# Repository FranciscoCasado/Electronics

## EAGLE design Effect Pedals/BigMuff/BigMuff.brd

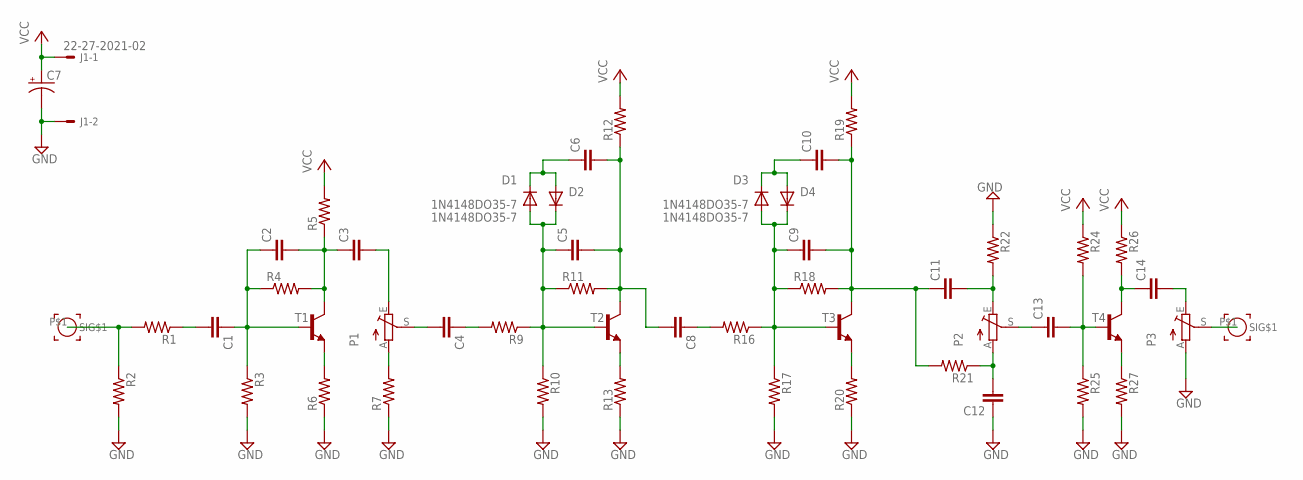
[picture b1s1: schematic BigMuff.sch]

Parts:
C1, C2, C3, C4, C5, C6, C8, C9, C10, C11, C12, C13, C14: C-EU050-024X044-BP; C050-024X044-BP
C7: CPOL-USE2.5-7; E2,5-7
D1, D2, D3, D4: 1N4148DO35-7; DO35-7
J1: 22-27-2021-02; 6410-02
P1, P2, P3: TRIM_EU-S64W; S64W
R1, R2, R3, R4, R5, R6, R7, R9, R10, R11, R12, R13, R16, R17, R18, R19, R20, R21, R22, R24, R25, R26, R27: R-US_0204/5-BP; 0204/5-BP
T1, T2, T3, T4: -NPN-TO92-EBC; TO92-EBC
U$1, U$2: SIGNAL_PAD

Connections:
GND: C7.-, C12.1, J1.2, P3.A, R2.2, R3.2, R6.1, R7.1, R10.2, R13.1, R17.2, R20.1, R22.1, R25.2, R27.2
unnamed: R1.2, R2.1, U$1.P$1
unnamed: C1.2, R1.1
unnamed: C1.1, C2.1, R3.1, R4.1, T1.B
unnamed: C2.2, C3.1, R4.2, R5.1, T1.C
unnamed: R6.2, T1.E
unnamed: P1.A, R7.2
unnamed: C3.2, P1.E
unnamed: C4.2, P1.S
unnamed: C4.1, R9.2
unnamed: C5.1, D1.A, D2.C, R9.1, R10.1, R11.1, T2.B
unnamed: C5.2, C6.2, C8.2, R11.2, R12.1, T2.C
unnamed: R13.2, T2.E
unnamed: C12.2, P2.A, R21.1
unnamed: C11.2, P2.E, R22.2
unnamed: C6.1, D1.C, D2.A
unnamed: C8.1, R16.2
unnamed: C9.1, D3.A, D4.C, R16.1, R17.1, R18.1, T3.B
unnamed: C9.2, C10.2, C11.1, R18.2, R19.1, R21.2, T3.C
unnamed: R20.2, T3.E
unnamed: C10.1, D3.C, D4.A
unnamed: C13.1, P2.S
unnamed: C13.2, R24.2, R25.1, T4.B
unnamed: C14.1, R26.2, T4.C
unnamed: R27.1, T4.E
unnamed: C14.2, P3.E
unnamed: P3.S, U$2.P$1
VCC: C7.+, J1.1, R5.2, R12.2, R19.2, R24.1, R26.1

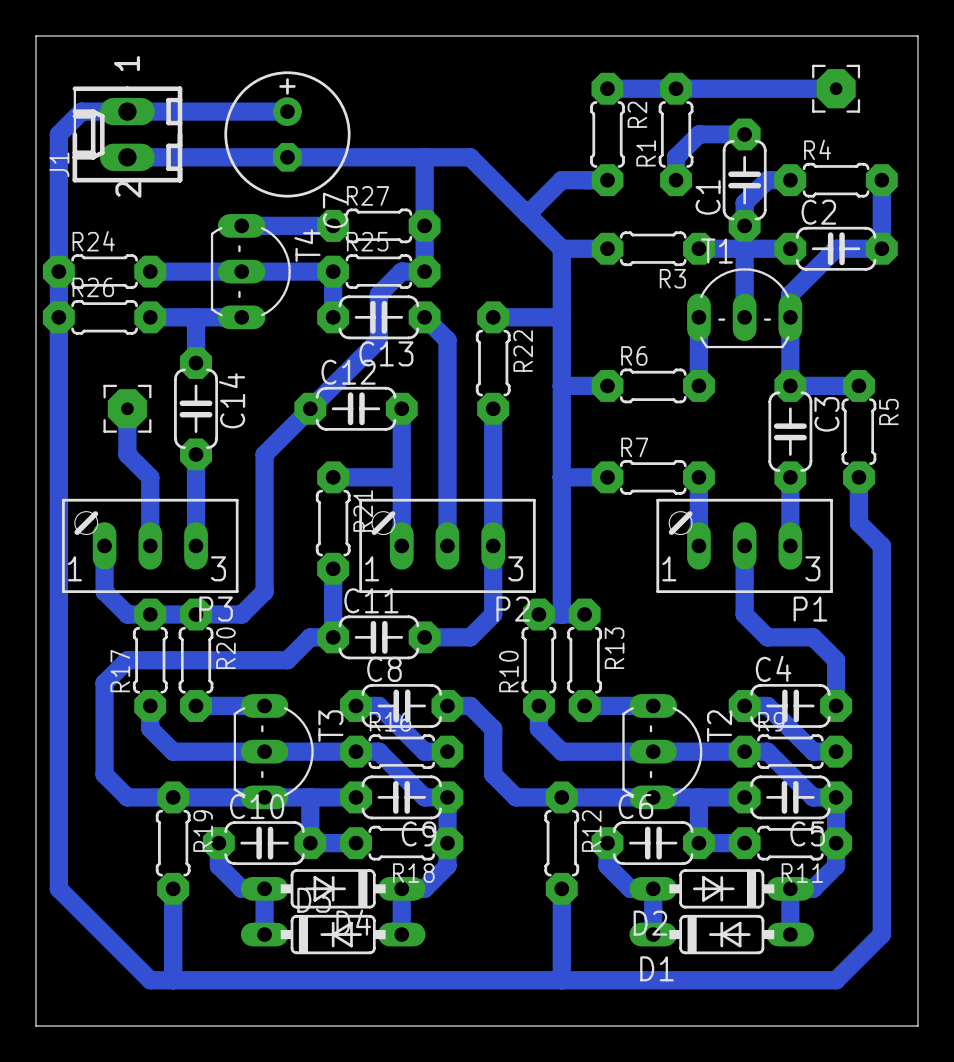
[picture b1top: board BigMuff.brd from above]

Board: 2 copper layers, 49.0 x 55.0 mm, 51 parts (0 on the bottom side), 28 nets.

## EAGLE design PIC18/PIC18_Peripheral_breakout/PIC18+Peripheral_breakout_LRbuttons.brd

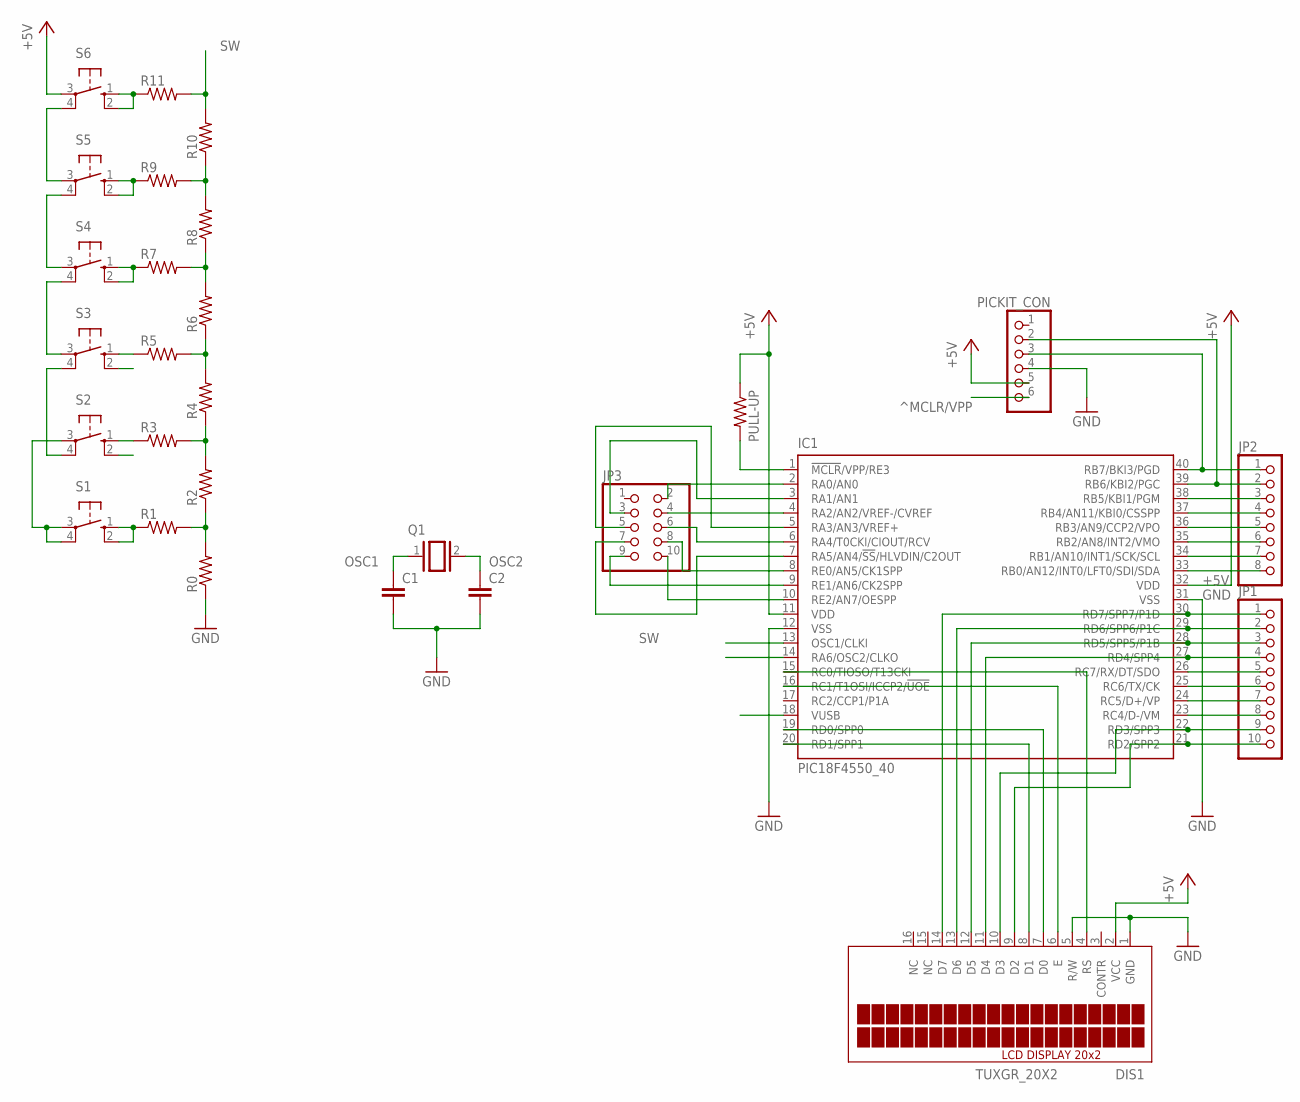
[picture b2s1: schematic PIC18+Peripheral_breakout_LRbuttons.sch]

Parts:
C1, C2: C-EUC1206; C1206
DIS1: TUXGR_20X2
IC1: PIC18F4550_40; DIL40
JP1: PINHD-1X10; 1X10
JP2: PINHD-1X8; 1X08
JP3: PINHD-2X5; 2X05
PICKIT_CON: PINHD-1X6/90; 1X06/90
PULL-UP: R-US_R1206; R1206
Q1: XTAL/S; QS
R0, R1, R2, R3, R4, R5, R6, R7, R8, R9, R10, R11: R-US_R1206; R1206
S1, S2, S3, S4, S5, S6: 10-XX; B3F-10XX

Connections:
+5V: DIS1.2 (VCC), IC1.11 (VDD), IC1.32 (VDD), PICKIT_CON.5, PULL-UP.1, S6.3
D0: DIS1.7 (D0), IC1.19 (RD0/SPP0)
D1: DIS1.8 (D1), IC1.20 (RD1/SPP1)
D2: DIS1.9 (D2), IC1.21 (RD2/SPP2), JP1.10
D3: DIS1.10 (D3), IC1.22 (RD3/SPP3), JP1.9
D4: DIS1.11 (D4), IC1.27 (RD4/SPP4), JP1.4
D5: DIS1.12 (D5), IC1.28 (RD5/SPP5/P1B), JP1.3
D6: DIS1.13 (D6), IC1.29 (RD6/SPP6/P1C), JP1.2
D7: DIS1.14 (D7), IC1.30 (RD7/SPP7/P1D), JP1.1
E: DIS1.6 (E), IC1.16 (RC1/T1OSI/ICCP2/!UOE)
GND: C1.2, C2.2, DIS1.1 (GND), DIS1.5 (R/W), IC1.12 (VSS), IC1.31 (VSS), PICKIT_CON.4, R0.1
unnamed: IC1.26 (RC7/RX/DT/SDO), JP1.5
unnamed: IC1.25 (RC6/TX/CK), JP1.6
unnamed: IC1.24 (RC5/D+/VP), JP1.7
unnamed: IC1.23 (RC4/D-/VM), JP1.8
unnamed: IC1.38 (RB5/KBI1/PGM), JP2.3
unnamed: IC1.37 (RB4/AN11/KBI0/CSSPP), JP2.4
unnamed: IC1.36 (RB3/AN9/CCP2/VPO), JP2.5
unnamed: IC1.35 (RB2/AN8/INT2/VMO), JP2.6
unnamed: IC1.34 (RB1/AN10/INT1/SCK/SCL), JP2.7
unnamed: IC1.33 (RB0/AN12/INT0/LFT0/SDI/SDA), JP2.8
unnamed: IC1.2 (RA0/AN0), JP3.2
unnamed: IC1.3 (RA1/AN1), JP3.3
unnamed: IC1.4 (RA2/AN2/VREF-/CVREF), JP3.4
unnamed: IC1.5 (RA3/AN3/VREF+), JP3.5
unnamed: IC1.6 (RA4/T0CKI/CIOUT/RCV), JP3.6
unnamed: IC1.8 (RE0/AN5/CK1SPP), JP3.8
unnamed: R0.2, R1.2, R2.1
unnamed: IC1.9 (RE1/AN6/CK2SPP), JP3.9
unnamed: IC1.7 (RA5/AN4/!SS!/HLVDIN/C2OUT), JP3.7
unnamed: R1.1, S1.1 (S), S1.2 (S1)
unnamed: R2.2, R3.2, R4.1
unnamed: R3.1, S2.1 (S)
unnamed: R5.1, S3.1 (S)
unnamed: R7.1, S4.1 (S), S4.2 (S1)
unnamed: R4.2, R5.2, R6.1
unnamed: R6.2, R7.2, R8.1
unnamed: R8.2, R9.2, R10.1
unnamed: S1.3, S1.4 (P1), S2.3
unnamed: R11.1, S6.1 (S), S6.2 (S1)
unnamed: R9.1, S5.1 (S), S5.2 (S1)
unnamed: S2.4 (P1), S3.4 (P1)
unnamed: S3.3, S4.4 (P1)
unnamed: S4.3, S5.4 (P1)
unnamed: S5.3, S6.4 (P1)
OSC1: C1.1, IC1.13 (OSC1/CLKI), Q1.1
OSC2: C2.1, IC1.14 (RA6/OSC2/CLKO), Q1.2
PGC: IC1.39 (RB6/KBI2/PGC), JP2.2, PICKIT_CON.2
PGD: IC1.40 (RB7/BKI3/PGD), JP2.1, PICKIT_CON.3
RS: DIS1.4 (RS), IC1.15 (RC0/TIOSO/T13CKI)
SW: IC1.10 (RE2/AN7/OESPP), JP3.10, R10.2, R11.2
^MCLR/VPP: IC1.1 (!MCLR!/VPP/RE3), PICKIT_CON.6, PULL-UP.2

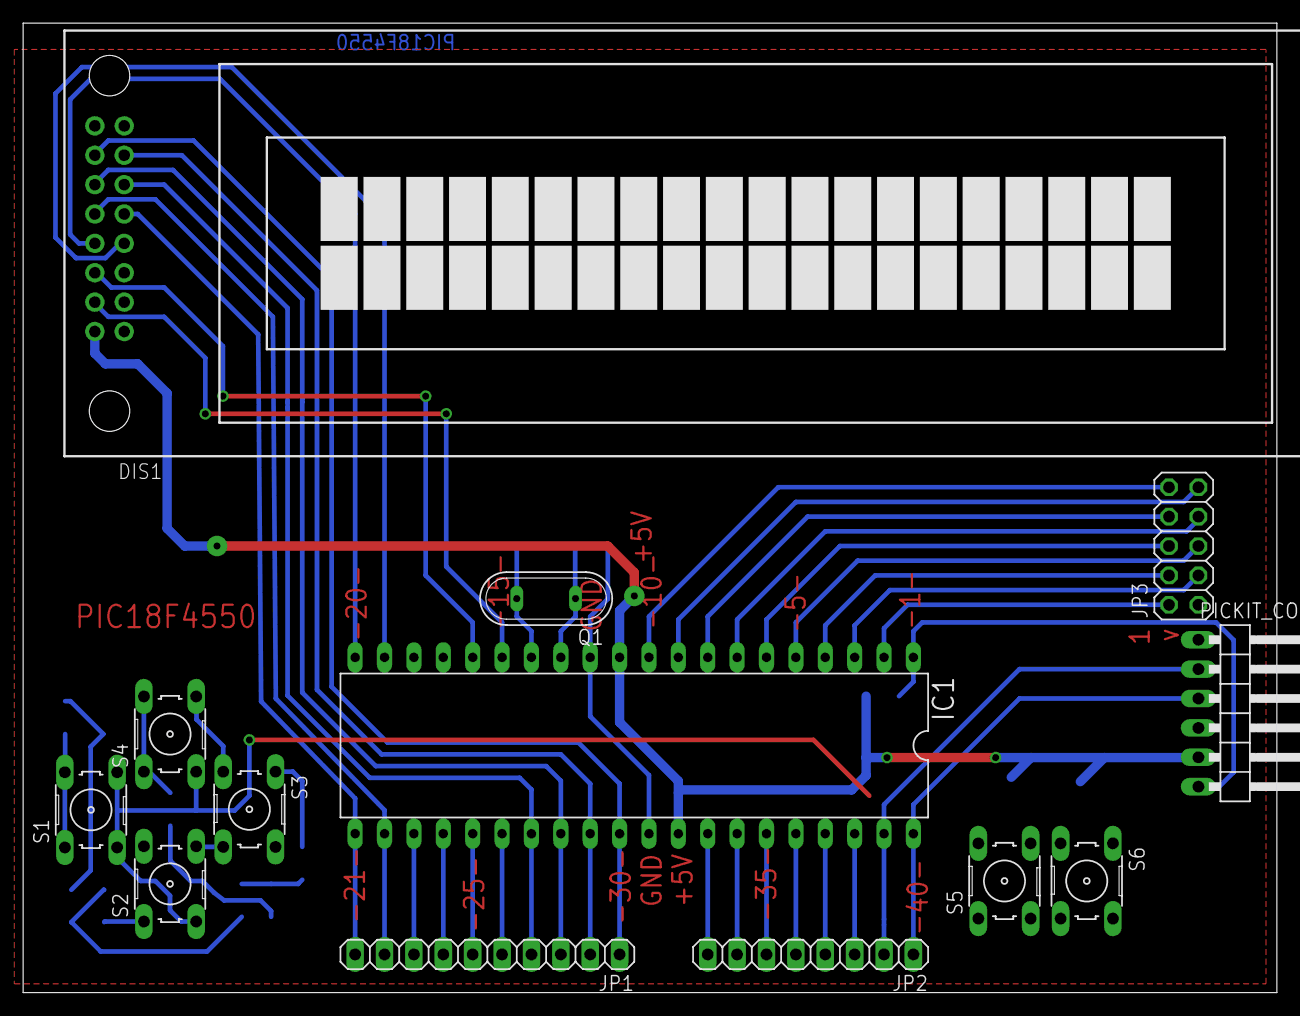
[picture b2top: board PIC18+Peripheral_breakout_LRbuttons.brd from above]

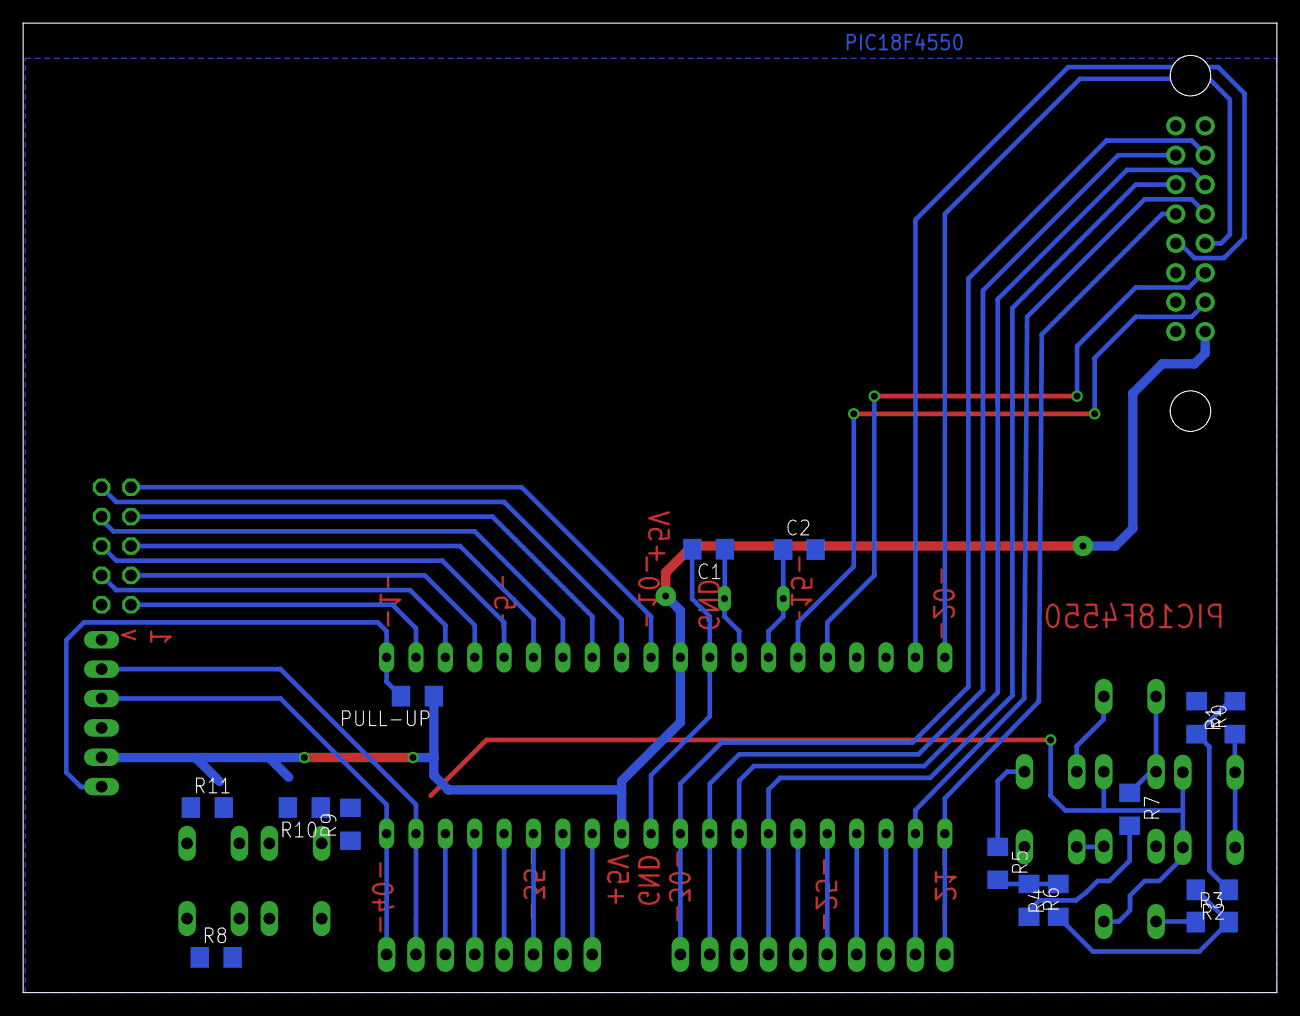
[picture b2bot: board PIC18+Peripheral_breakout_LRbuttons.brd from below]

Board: 2 copper layers, 108.4 x 83.8 mm, 28 parts (15 on the bottom side), 52 nets.

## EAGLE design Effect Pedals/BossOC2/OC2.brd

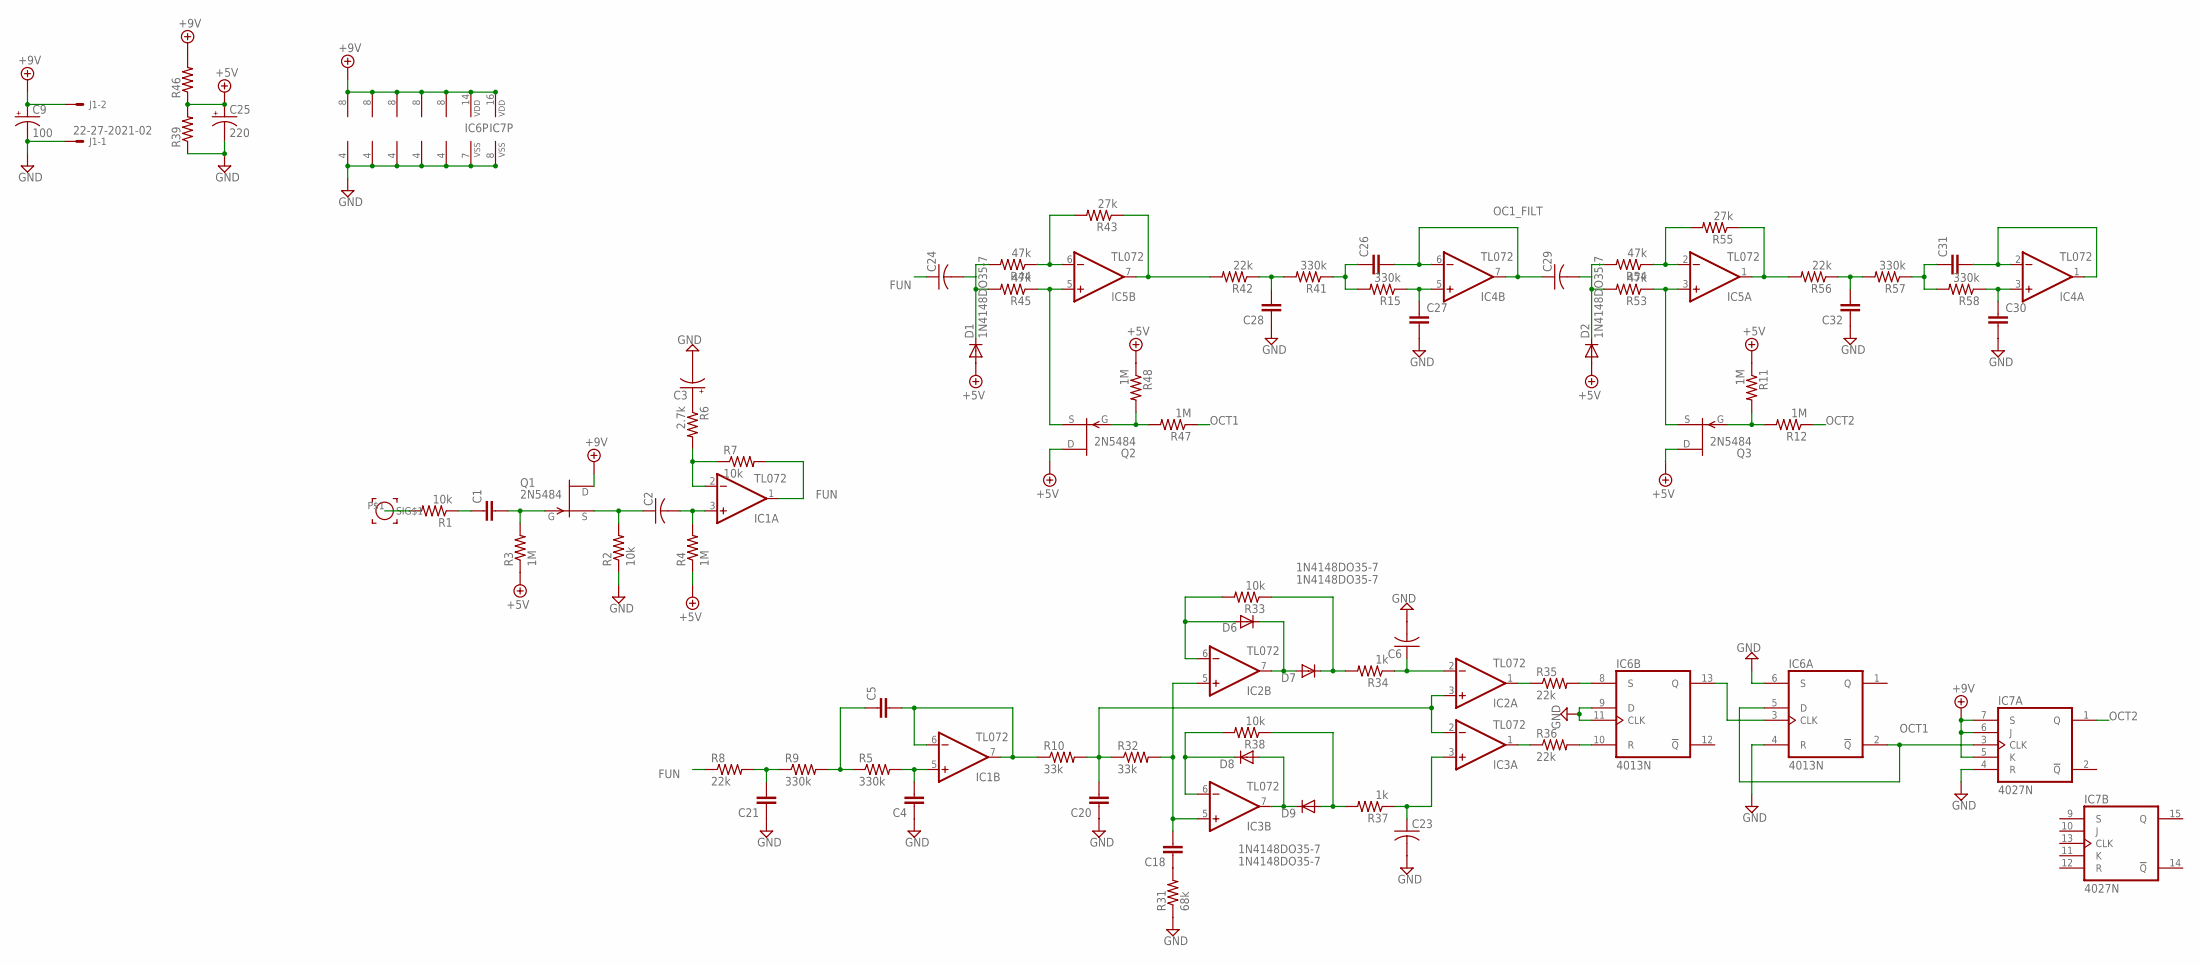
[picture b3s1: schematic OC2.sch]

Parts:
C1, C4, C5, C18, C20, C21, C26, C27, C28, C30, C31, C32: C-EU; C025-025X050-BP
C2, C6, C23, C24, C29: C-US; C050-024X044-BP
C3: CPOL-USE2.5-5; E2,5-5
C9: 100; E2,5-6
C25: 220; E3,5-8
D1, D2, D6, D7, D8, D9: 1N4148DO35-7; DO35-7
IC1, IC2, IC3, IC4, IC5: TL072; DIL08-BP
IC6: 4013N; DIL14
IC7: 4027N; DIL16
INPUT: SIGNAL_PAD
J1: 22-27-2021-02; 6410-02
Q1, Q2, Q3: 2N5484; TO92-
R1, R2, R7, R33, R38: 10k; 0204V-BP
R3, R4, R11, R12, R47, R48: 1M; 0204V-BP
R5, R15, R41, R57, R58: 330k; 0204V-BP
R6: 2.7k; 0204V-BP
R8: 22k; 0204V
R9: 330k; 0204/5
R10, R32: 33k; 0204V-BP
R31: 68k; 0204V-BP
R34, R37: 1k; 0204V-BP
R35, R42, R56: 22k; 0204V-BP
R36: 22k; 0204/5
R39, R46: R-US_; 0204V-BP
R43, R55: 27k; 0204V-BP
R44, R45, R53, R54: 47k; 0204V-BP

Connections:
+5V: C25.+, D1.A, D2.A, Q2.3 (D), Q3.3 (D), R3.1, R4.1, R11.1, R39.2, R46.1, R48.1
+9V: C9.+, IC1.8 (V+), IC2.8 (V+), IC3.8 (V+), IC4.8 (V+), IC5.8 (V+), IC6.14 (VDD), IC7.5 (K), IC7.6 (J), IC7.7 (S), IC7.16 (VDD), J1.2, Q1.3 (D), R46.2
FUN: C24.1, IC1.1 (OUT), R7.2, R8.1
GND: C3.-, C4.1, C6.2, C9.-, C20.1, C21.1, C23.2, C25.-, C27.2, C28.1, C30.2, C32.1, IC1.4 (V-), IC2.4 (V-), IC3.4 (V-), IC4.4 (V-), IC5.4 (V-), IC6.4 (R), IC6.6 (S), IC6.7 (VSS), IC6.9 (D), IC6.11 (CLK), IC7.4 (R), IC7.8 (VSS), J1.1, R2.1, R31.1, R39.1
unnamed: IC1.2 (-IN), R6.2, R7.1
unnamed: C3.+, R6.1
unnamed: Q2.1 (G), R47.2, R48.2
unnamed: C2.1, Q1.2 (S), R2.2
unnamed: C2.2, IC1.3 (+IN), R4.2
unnamed: IC6.8 (S), R35.2
unnamed: IC2.1 (OUT), R35.1
unnamed: IC3.1 (OUT), R36.1
unnamed: IC6.10 (R), R36.2
unnamed: INPUT.P$1, R1.2
unnamed: IC6.3 (CLK), IC6.13 (Q)
unnamed: IC5.5 (+IN), Q2.2 (S), R45.1
unnamed: C1.1, R1.1
unnamed: C1.2, Q1.1 (G), R3.2
unnamed: C21.2, R8.2, R9.1
unnamed: C5.1, R5.1, R9.2
unnamed: C4.2, IC1.5 (+IN), R5.2
unnamed: C5.2, IC1.6 (-IN), IC1.7 (OUT), R10.1
unnamed: C20.2, IC2.3 (+IN), IC3.2 (-IN), R10.2, R32.1
unnamed: C18.2, IC2.5 (+IN), IC3.5 (+IN), R32.2
unnamed: C18.1, R31.2
unnamed: D8.C, IC3.6 (-IN), R38.2
unnamed: D8.A, D9.C, IC3.7 (OUT)
unnamed: D6.C, D7.A, IC2.7 (OUT)
unnamed: D6.A, IC2.6 (-IN), R33.2
unnamed: C6.1, IC2.2 (-IN), R34.1
unnamed: D9.A, R37.2, R38.1
unnamed: C23.1, IC3.3 (+IN), R37.1
unnamed: D7.C, R33.1, R34.2
unnamed: Q3.1 (G), R11.2, R12.2
unnamed: IC5.3 (+IN), Q3.2 (S), R53.1
unnamed: C24.2, D1.C, R44.2, R45.2
unnamed: C29.2, D2.C, R53.2, R54.2
unnamed: IC5.6 (-IN), R43.2, R44.1
unnamed: IC5.2 (-IN), R54.1, R55.2
unnamed: IC5.1 (OUT), R55.1, R56.2
unnamed: IC5.7 (OUT), R42.2, R43.1
unnamed: C30.1, IC4.3 (+IN), R58.1
unnamed: C27.1, IC4.5 (+IN), R15.1
unnamed: C26.1, R15.2, R41.1
unnamed: C28.2, R41.2, R42.1
unnamed: C31.1, R57.1, R58.2
unnamed: C32.2, R56.1, R57.2
OC1_FILT: C26.2, C29.1, IC4.6 (-IN), IC4.7 (OUT)
OC1_FILT2: C31.2, IC4.1 (OUT), IC4.2 (-IN)
OCT1: IC6.2 (!Q), IC6.5 (D), IC7.3 (CLK), R47.1
OCT2: IC7.1 (Q), R12.1

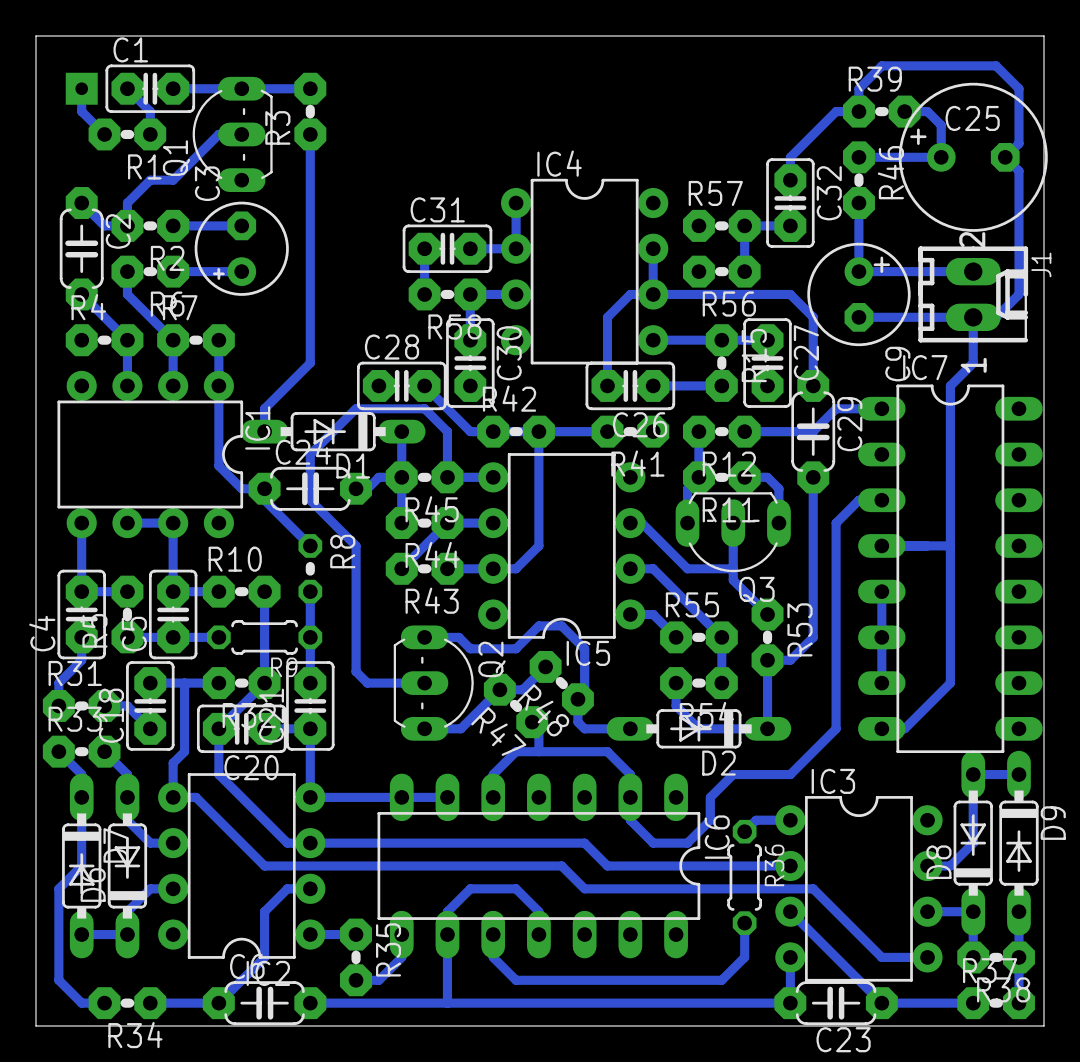
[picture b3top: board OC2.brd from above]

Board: 2 copper layers, 56.0 x 55.0 mm, 74 parts (0 on the bottom side), 51 nets.

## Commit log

2017-03-11 initial commit with some projects
2017-03-11 BigMuff ready to print
